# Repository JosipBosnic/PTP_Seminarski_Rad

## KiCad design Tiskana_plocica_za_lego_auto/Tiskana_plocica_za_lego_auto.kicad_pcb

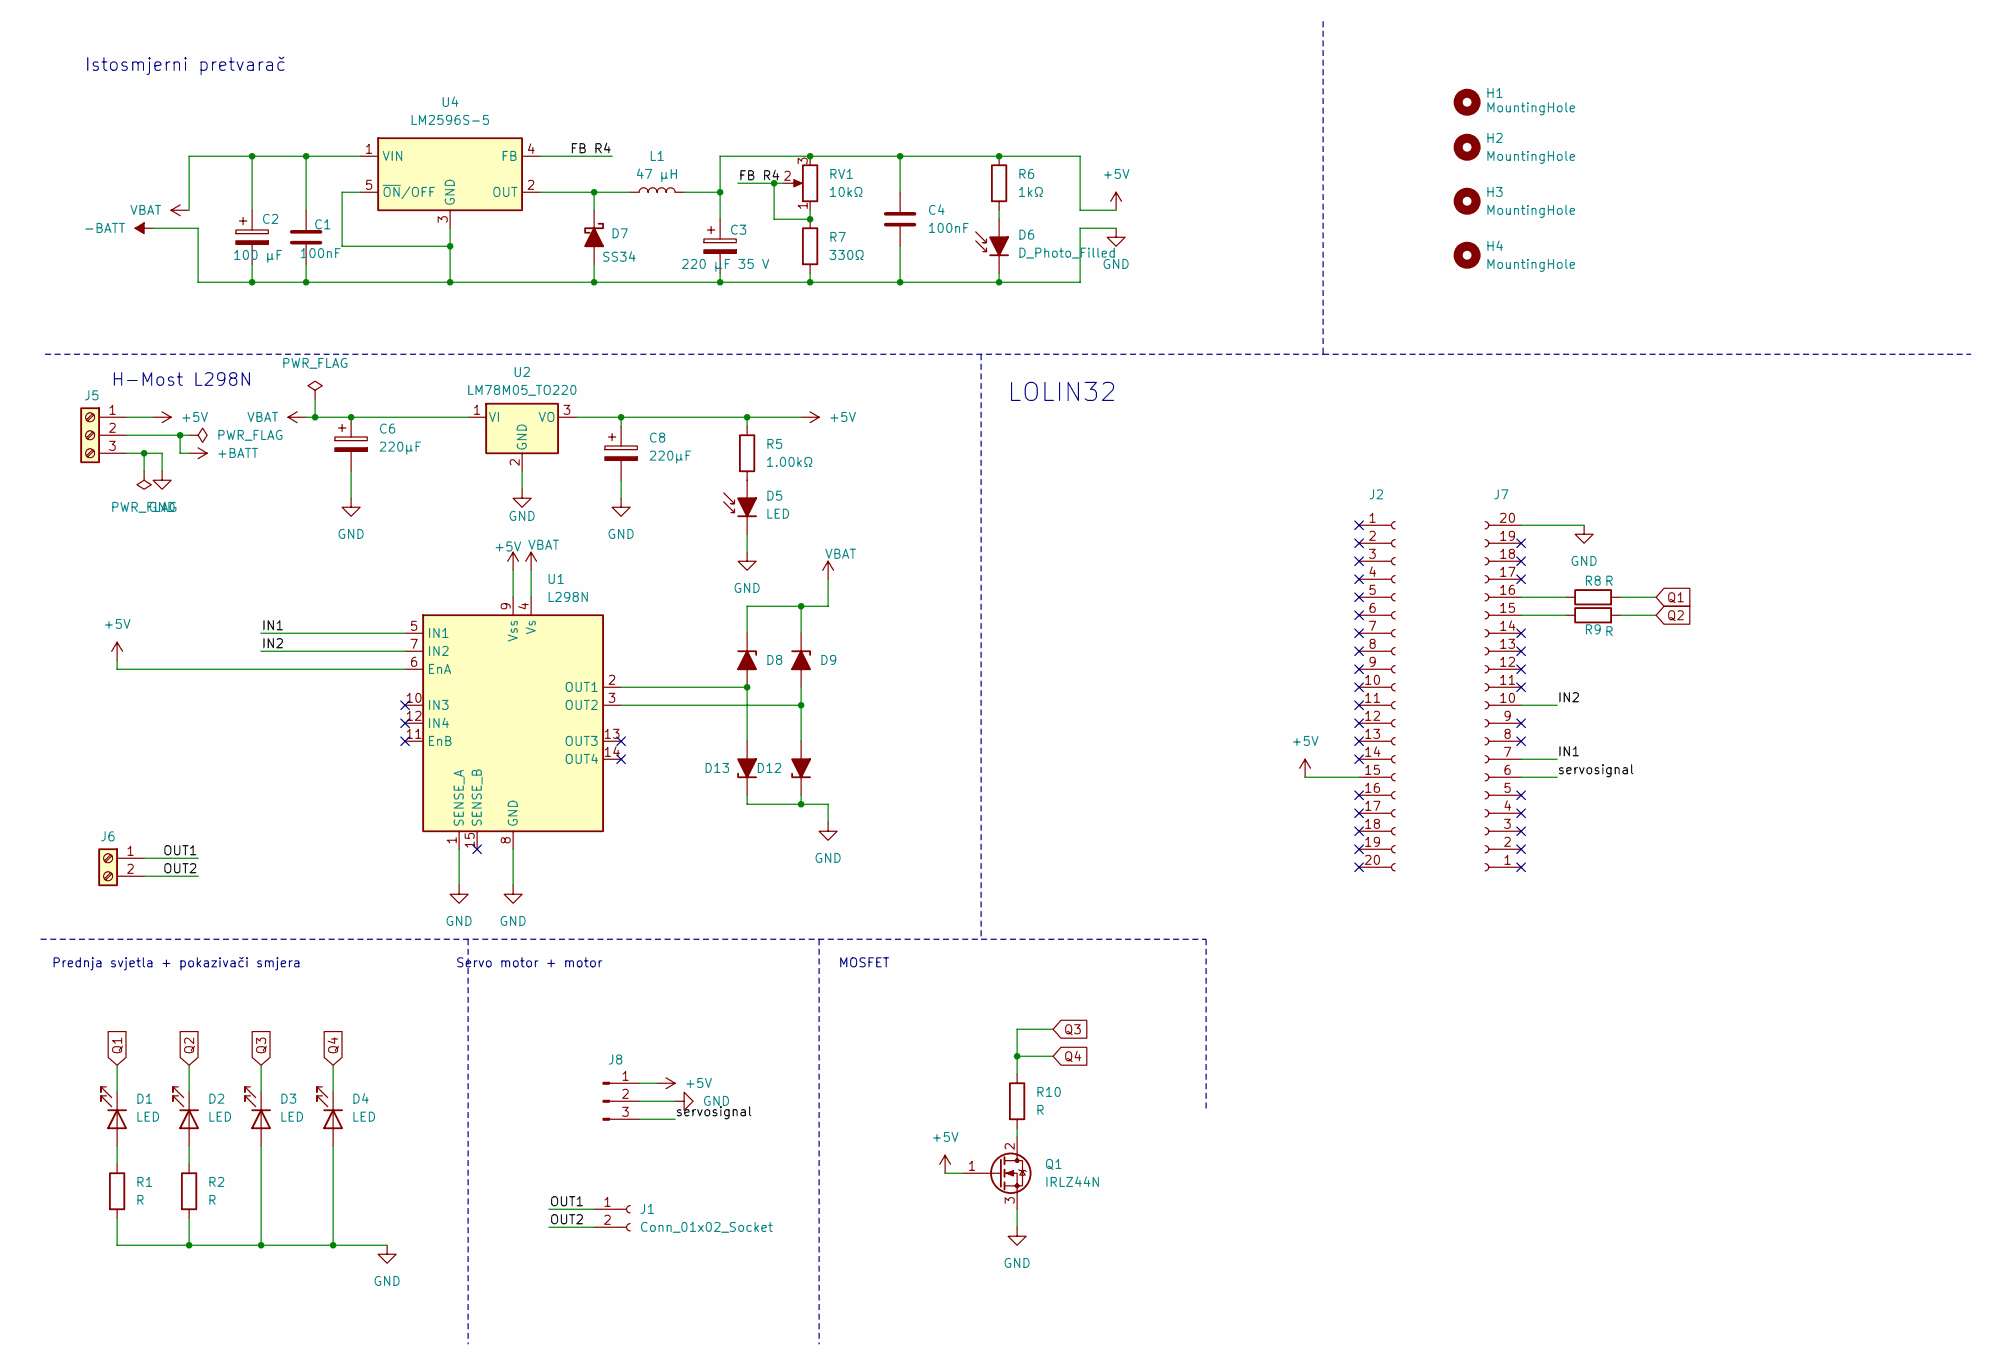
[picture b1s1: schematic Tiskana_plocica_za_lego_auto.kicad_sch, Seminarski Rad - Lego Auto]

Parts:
C1, C4: 100nF; C_0805_2012Metric
C2: 100 μF; CP_Radial_D5.0mm_P2.00mm
C3: 220 μF 35 V; CP_Elec_8x5.4
C6, C8: 220μF; CP_Elec_8x5.4
D1, D2, D3, D4, D5: LED; LED_0805_2012Metric
D6: D_Photo_Filled; Osram_BPW34S-SMD
D7: SS34; D_0805_2012Metric
D8, D9, D12, D13: D_Zener_Filled; D_0805_2012Metric
H1, H2, H3, H4: MountingHole; MountingHole_8.4mm_M8
J1: Conn_01x02_Socket; PinHeader_1x02_P2.54mm_Vertical_SMD_Pin1Right
J2: Conn_01x20_Socket; PinHeader_1x20_P2.54mm_Vertical_SMD_Pin1Left
J5: TerminalBlock_Phoenix_PTSM-0,5-3-2,5-V-SMD_1x03-1MP_P2.50mm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
J6: Screw_Terminal_01x02; TerminalBlock_Phoenix_PTSM-0,5-2-2,5-V-SMD_1x02-1MP_P2.50mm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
J7: Conn_01x20_Socket; PinSocket_1x20_P2.54mm_Vertical_SMD_Pin1Right
J8: Conn_01x03_Pin; PinHeader_1x03_P2.54mm_Vertical_SMD_Pin1Right
L1: 47 μH; L_Neosid_Ms85
Q1: IRLZ44N; TO-220-3_Vertical
R1, R2, R8, R9, R10: R; R_0805_2012Metric
R5: 1.00kΩ; R_0805_2012Metric
R6: 1kΩ; R_0805_2012Metric
R7: 330Ω; R_0805_2012Metric
RV1: 10kΩ; Potentiometer_ACP_CA6-VSMD_Vertical
U1: L298N; TO-220-15_P2.54x5.08mm_StaggerOdd_Lead4.58mm_Vertical
U2: LM78M05_TO220; TO-220-3_Vertical
U4: LM2596S-5; TO-263-5_TabPin3

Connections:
+5V: C3.1, C4.1, C8.1, J2.15, J5.1, J8.1, L1.2, Q1.1 (G), R5.1, R6.1, RV1.3, U1.6 (EnA), U1.9 (Vss), U2.3 (VO)
+BATT: J5.2
-BATT: C1.2, C2.2, C3.2, C4.2, C6.2, C8.2, D3.2 (A), D4.2 (A), D5.1 (K), D6.1 (K), D7.2 (A), D12.1 (K), D13.1 (K), J5.3, J7.20, J8.2, Q1.3 (S), R1.2, R2.2, R7.2, U1.1 (SENSE_A), U1.8 (GND), U2.2 (GND), U4.3 (GND), U4.5 (~ON/OFF)
/FB R4: R7.1, RV1.1, RV1.2, U4.4 (FB)
/IN1: J7.7, U1.5 (IN1)
/IN2: J7.10, U1.7 (IN2)
/OUT1: J1.1, J6.1
/OUT2: J1.2, J6.2
/servosignal: J7.6, J8.3
unnamed: D1.2 (A), R1.1
unnamed: D2.2 (A), R2.1
unnamed: D5.2 (A), R5.2
unnamed: D6.2 (A), R6.2
unnamed: D7.1 (K), L1.1, U4.2 (OUT)
unnamed: D9.2 (A), D12.2 (A), U1.3 (OUT2)
unnamed: D8.2 (A), D13.2 (A), U1.2 (OUT1)
unnamed: J7.15, R9.1
unnamed: J7.16, R8.1
unnamed: Q1.2 (D), R10.2
Q1: D1.1 (K), R8.2
Q2: D2.1 (K), R9.2
Q3: D3.1 (K), D4.1 (K), R10.1
VBAT: C1.1, C2.1, C6.1, D8.1 (K), D9.1 (K), U1.4 (Vs), U2.1 (VI), U4.1 (VIN)

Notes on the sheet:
Servo motor + motor
H-Most L298N
MOSFET
Istosmjerni pretvarač
Prednja svjetla + pokazivači smjera
LOLIN32

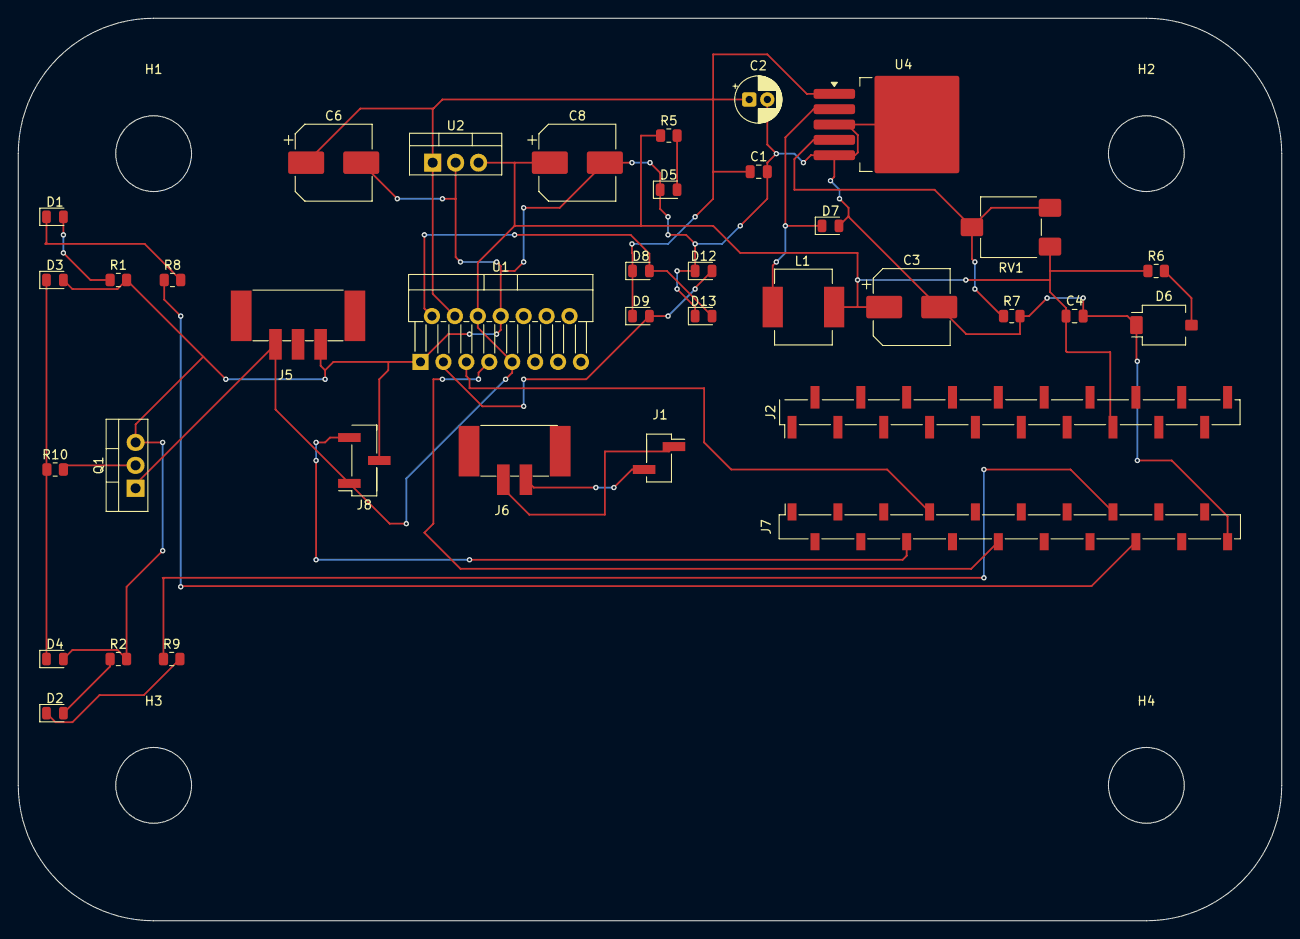
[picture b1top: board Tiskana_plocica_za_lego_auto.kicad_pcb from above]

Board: 2 copper layers, 140.0 x 100.0 mm, 41 parts (0 on the bottom side), 22 nets.

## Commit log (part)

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2026-01-20 seminarski_rad_1
2026-01-27 seminarskirad2
